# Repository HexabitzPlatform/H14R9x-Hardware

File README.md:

# H14R9x-Hardware
Hexabitz 4 x 5V PWM O/P  + External Supply Module Hardware Design

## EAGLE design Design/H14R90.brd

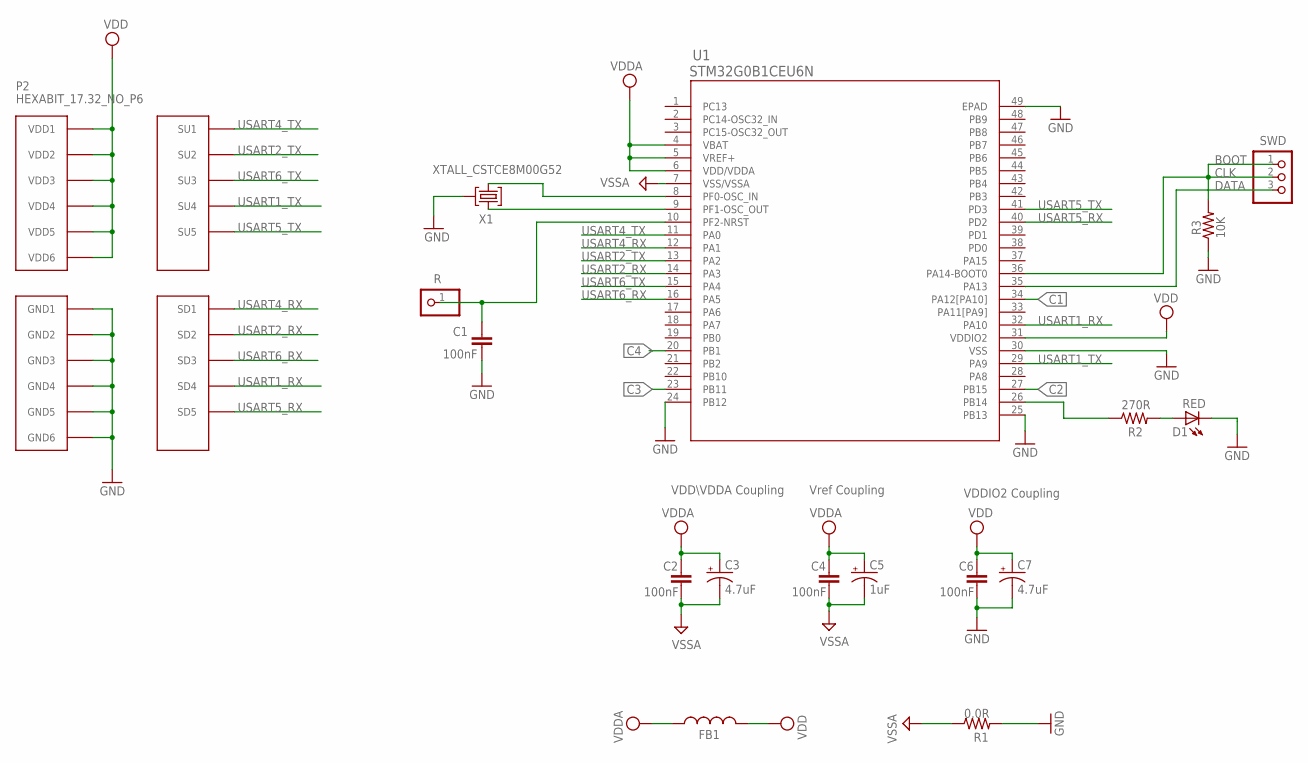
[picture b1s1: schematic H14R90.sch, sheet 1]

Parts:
C1, C2, C4, C6: 100nF; C-0603
C3, C7: 4.7uF; C-0805-POL
C5: 1uF; C-0805-POL
D1: RED; VLMS1300-GS08; MPN VLMS1300-GS08
FB1: FB-0603
P2: HEXABIT_17.32_NO_P6
R: R; 1X01
R1: 0.0R; R-0603
R2: 270R; R-0603
R3: 10K; R-0603
SWD: PINHD-1X3; 1X03
U1: STM32G0B1CEU6N; HEXABITZ_ICS_QFN_B1CEU6_STM-L
X1: XTALL_CSTCE8M00G52

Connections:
C1: U1.34 (PA12[PA10]); also elsewhere on the board
C2: U1.27 (PB15); also elsewhere on the board
C3: U1.23 (PB11); also elsewhere on the board
C4: U1.20 (PB1); also elsewhere on the board
CLK: R3.2, SWD.1, SWD.2, U1.36 (PA14-BOOT0)
DATA: SWD.3, U1.35 (PA13)
GND: C1.2, C6.2, C7.2 (-), D1.C, P2.PAD_PD7 (GND1), P2.PAD_PD8 (GND2), P2.PAD_PD9 (GND3), P2.PAD_PD10 (GND4), P2.PAD_PD11 (GND5), P2.PAD_PD12 (GND6), R1.2, R3.1, U1.24 (PB12), U1.25 (PB13), U1.30 (VSS), U1.49 (EPAD), X1.P$2 (2)
unnamed: D1.A, R2.2
unnamed: U1.9 (PF1-OSC_OUT), X1.P$1 (1)
unnamed: U1.8 (PF0-OSC_IN), X1.P$3 (3)
unnamed: C1.1, R.1, U1.10 (PF2-NRST)
unnamed: R2.1, U1.26 (PB14)
USART1_RX: P2.PAD_PD4 (SD4), U1.32 (PA10)
USART1_TX: P2.PAD_PU4 (SU4), U1.29 (PA9)
USART2_RX: P2.PAD_PD2 (SD2), U1.14 (PA3)
USART2_TX: P2.PAD_PU2 (SU2), U1.13 (PA2)
USART4_RX: P2.PAD_PD1 (SD1), U1.12 (PA1)
USART4_TX: P2.PAD_PU1 (SU1), U1.11 (PA0)
USART5_RX: P2.PAD_PD5 (SD5), U1.40 (PD2)
USART5_TX: P2.PAD_PU5 (SU5), U1.41 (PD3)
USART6_RX: P2.PAD_PD3 (SD3), U1.16 (PA5)
USART6_TX: P2.PAD_PU3 (SU3), U1.15 (PA4)
VDD: C6.1, C7.1 (+), FB1.2, P2.PAD_PU7 (VDD1), P2.PAD_PU8 (VDD2), P2.PAD_PU9 (VDD3), P2.PAD_PU10 (VDD4), P2.PAD_PU11 (VDD5), P2.PAD_PU12 (VDD6), U1.31 (VDDIO2)
VDDA: C2.1, C3.1 (+), C4.1, C5.1 (+), FB1.1, U1.4 (VBAT), U1.5 (VREF+), U1.6 (VDD/VDDA); also elsewhere on the board
VSSA: C2.2, C3.2 (-), C4.2, C5.2 (-), R1.1, U1.7 (VSS/VSSA); also elsewhere on the board

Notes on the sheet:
Vref Coupling
VDDIO2 Coupling
VDD\VDDA Coupling
BOOT

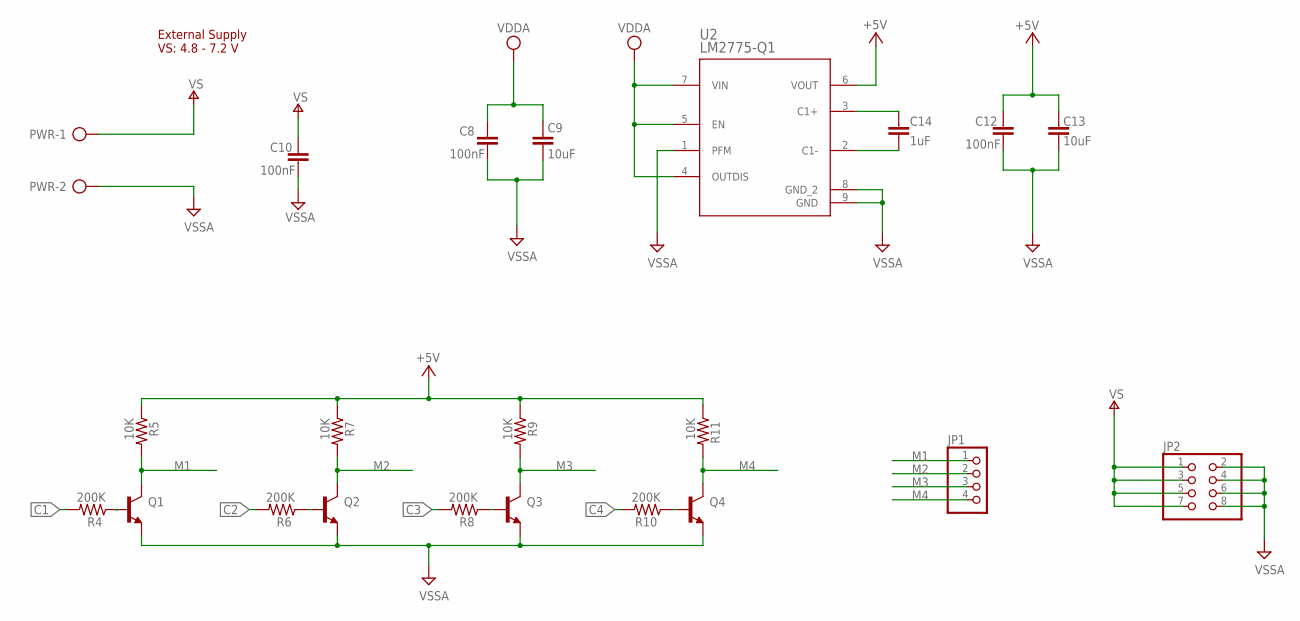
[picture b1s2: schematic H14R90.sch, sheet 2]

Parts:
C8, C10, C12: 100nF; C-0603
C9, C13: 10uF; C-0603
C14: 1uF; C-0603
JP1: PINHD-1X4; 1X04
JP2: PINHD-2X4; 2X04
PWR: AK500/2
Q1, Q2, Q3, Q4: MMBT3904LT1
R4, R6, R8, R10: 200K; R-0603
R5, R7, R9, R11: 10K; R-0603
U2: LM2775-Q1; DSG0008A

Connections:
+5V: C12.1, C13.1, R5.1, R7.1, R9.1, R11.1, U2.6 (VOUT)
C1: R4.2; also elsewhere on the board
C2: R6.2; also elsewhere on the board
C3: R8.2; also elsewhere on the board
C4: R10.2; also elsewhere on the board
M1: JP1.1, Q1.3 (C), R5.2
M2: JP1.2, Q2.3 (C), R7.2
M3: JP1.3, Q3.3 (C), R9.2
M4: JP1.4, Q4.3 (C), R11.2
unnamed: C14.2, U2.2 (C1-)
unnamed: C14.1, U2.3 (C1+)
unnamed: Q1.1 (B), R4.1
unnamed: Q2.1 (B), R6.1
unnamed: Q3.1 (B), R8.1
unnamed: Q4.1 (B), R10.1
V+: C10.1, JP2.1, JP2.3, JP2.5, JP2.7, PWR.1
VDDA: C8.1, C9.1, U2.4 (OUTDIS), U2.5 (EN), U2.7 (VIN); also elsewhere on the board
VSSA: C8.2, C9.2, C10.2, C12.2, C13.2, JP2.2, JP2.4, JP2.6, JP2.8, PWR.2, Q1.2 (E), Q2.2 (E), Q3.2 (E), Q4.2 (E), U2.1 (PFM), U2.8 (GND_2), U2.9 (GND); also elsewhere on the board

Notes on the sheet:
External Supply VS: 4.8 - 7.2 V

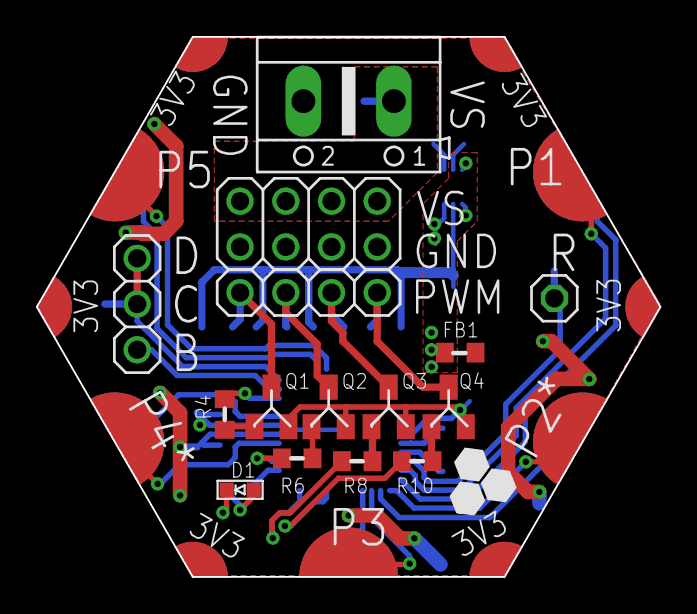
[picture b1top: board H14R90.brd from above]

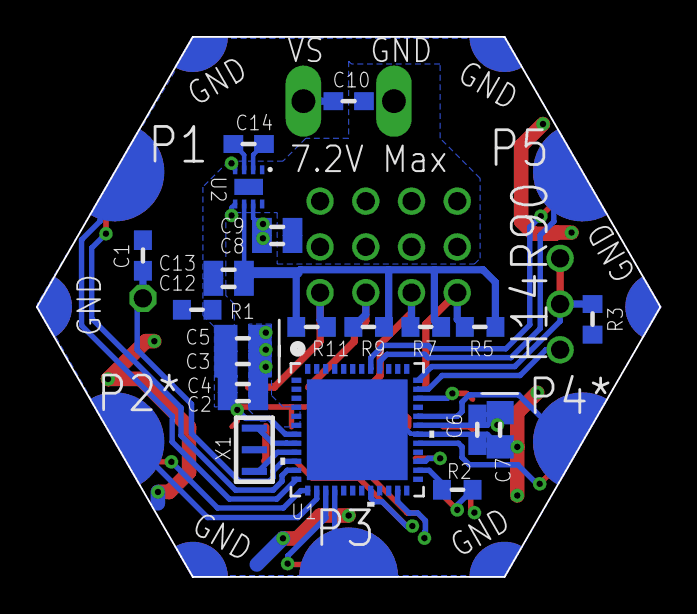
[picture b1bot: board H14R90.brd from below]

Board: 2 copper layers, 34.6 x 30.0 mm, 39 parts (23 on the bottom side), 37 nets.

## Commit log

2023-09-16 - First Version
2023-11-16 -Fix the outputs pin headers spacing
2023-11-16 -Correcting some documentaion issues

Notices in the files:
parts and their libraries:
HEXABITZ_ICs: COPYRIGHT: Copyright (C) 2022 Ultra Librarian. All rights reserved.
